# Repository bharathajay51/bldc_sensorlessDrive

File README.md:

# bldc_sensorlessDrive
Development of a 3-Phase Brushless Motor Driver.

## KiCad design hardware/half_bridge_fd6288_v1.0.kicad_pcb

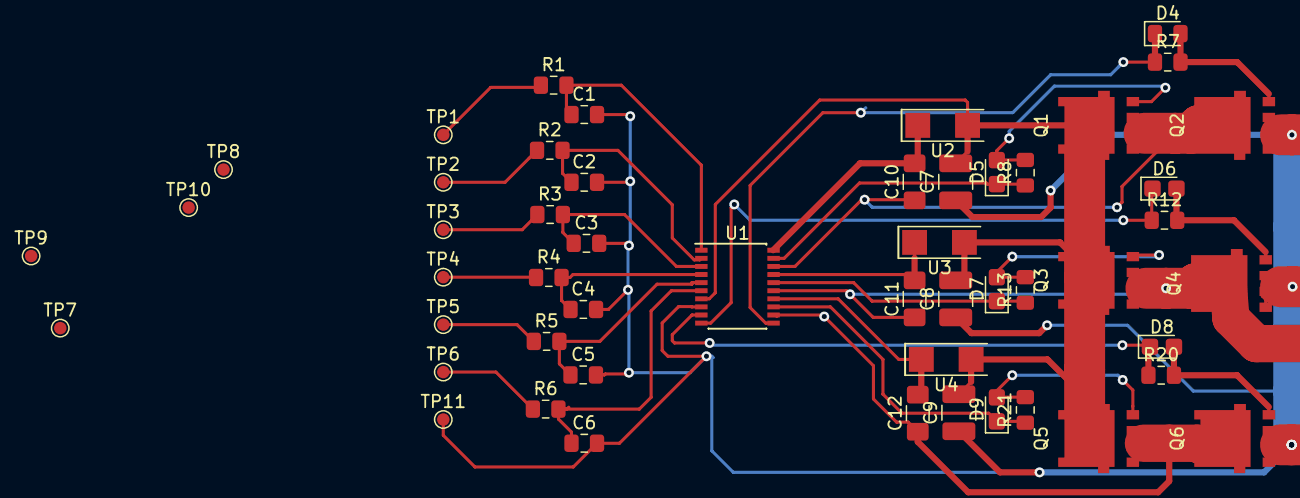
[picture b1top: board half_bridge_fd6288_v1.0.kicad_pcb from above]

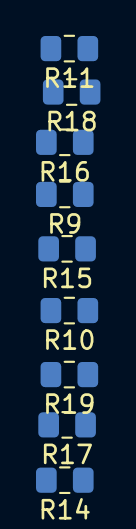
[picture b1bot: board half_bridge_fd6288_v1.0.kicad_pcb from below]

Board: 2 copper layers, 60 parts (9 on the bottom side), 36 nets.

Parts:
C1, C2, C3, C4, C5, C6: 33pF; C_0805_2012Metric_Pad1.15x1.40mm_HandSolder
C7, C8, C9: 1uF; C_1210_3225Metric_Pad1.42x2.65mm_HandSolder
C10, C11, C12: 100nF; C_1206_3216Metric_Pad1.42x1.75mm_HandSolder
D4: 1N4148; D_0805_2012Metric_Pad1.15x1.40mm_HandSolder
D5, D6, D7, D8, D9: 1N4148; D_0805_2012Metric_Castellated
Q1, Q2, Q3, Q4, Q5, Q6: Q_NMOS_DGS; NTMS5C430
R1, R2, R3, R4, R5, R6: 49.9; R_0805_2012Metric_Pad1.15x1.40mm_HandSolder
R7, R8, R12, R13, R20, R21: 3.3; R_0805_2012Metric_Pad1.15x1.40mm_HandSolder
R9, R14, R17: 33K; R_0805_2012Metric_Pad1.15x1.40mm_HandSolder
R10, R15, R18: 120K; R_0805_2012Metric_Pad1.15x1.40mm_HandSolder
R11, R16, R19: 3.3K; R_0805_2012Metric_Pad1.15x1.40mm_HandSolder
TP1: HIN_A; TestPoint_Pad_D1.0mm
TP2: HIN_B; TestPoint_Pad_D1.0mm
TP3: HIN_C; TestPoint_Pad_D1.0mm
TP4: LIN_A; TestPoint_Pad_D1.0mm
TP5: LIN_B; TestPoint_Pad_D1.0mm
TP6: LIN_C; TestPoint_Pad_D1.0mm
TP7: SENSE_A; TestPoint_Pad_D1.0mm
TP8: SENSE_B; TestPoint_Pad_D1.0mm
TP9, TP10: SENSE_C; TestPoint_Pad_D1.0mm
TP11: GND; TestPoint_Pad_D1.0mm
U1: FD6288; SSOP-20_4.4x6.5mm_P0.65mm
U2, U3, U4: MURA110T3

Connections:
GH_A: D5.1, R8.1, U1.19
GH_B: D7.1, R13.1, U1.16
GH_C: D9.1, R21.1, U1.13
GL_A: D4.1, R7.1, U1.11
GL_B: D6.1, R12.1, U1.10
GL_C: D8.1, R20.1, U1.9
GND: C1.2, C2.2, C3.2, C4.2, C5.2, C6.2, C7.1, C8.1, C9.1, Q2.3, Q4.3, Q6.3, R9.2, R14.2, R17.2, TP11.1, U1.8
HIN_A: R1.1, TP1.1
HIN_B: R2.1, TP2.1
HIN_C: R3.1, TP3.1
LIN_A: R4.1, TP4.1
LIN_B: R5.1, TP5.1
LIN_C: R6.1, TP6.1
unnamed: C1.1, R1.2, U1.1
unnamed: C2.1, R2.2, U1.2
unnamed: C3.1, R3.2, U1.3
unnamed: C4.1, R4.2, U1.4
unnamed: C5.1, R5.2, U1.5
unnamed: C6.1, R6.2, U1.6
unnamed: C10.2, U1.20, U2.1
unnamed: C11.2, U1.17, U3.1
unnamed: C12.2, U1.14, U4.1
unnamed: D4.2, Q2.2, R7.2
unnamed: D5.2, Q1.2, R8.2
unnamed: D6.2, Q4.2, R12.2
unnamed: D7.2, Q3.2, R13.2
unnamed: D8.2, Q6.2, R20.2
unnamed: D9.2, Q5.2, R21.2
PHASE_A: C10.1, Q1.3, Q2.1, R10.1, U1.18
PHASE_B: C11.1, Q3.3, Q4.1, R15.1, U1.15
PHASE_C: C12.1, Q5.3, Q6.1, R18.1, U1.12
SENSE_A: R9.1, R10.2, R11.2, TP7.1
SENSE_B: R14.1, R15.2, R16.2, TP8.1
SENSE_C: R17.1, R18.2, R19.2, TP9.1
SENSE_COM: R11.1, R16.1, R19.1, TP10.1
VCC: C7.2, C8.2, C9.2, Q1.1, Q3.1, Q5.1, U1.7, U2.2, U3.2, U4.2

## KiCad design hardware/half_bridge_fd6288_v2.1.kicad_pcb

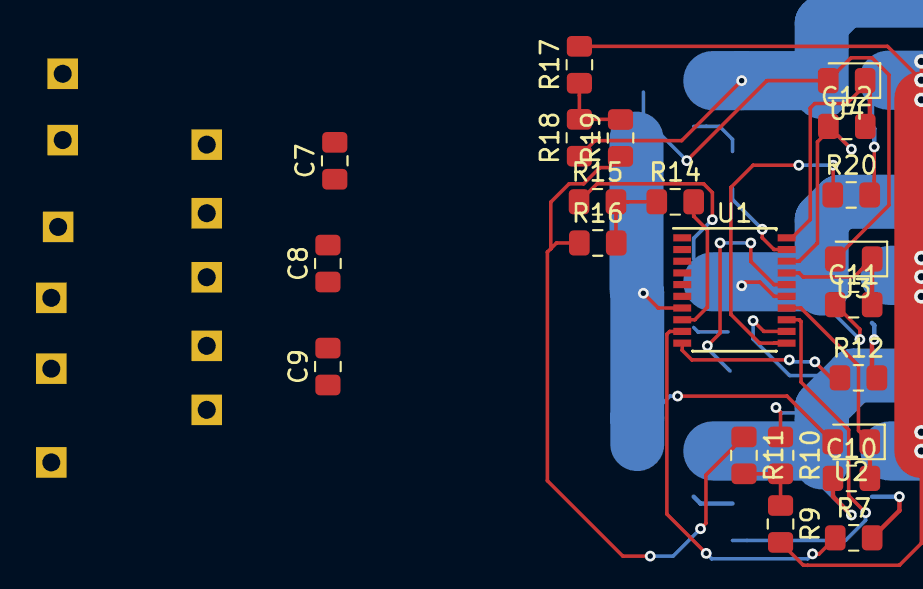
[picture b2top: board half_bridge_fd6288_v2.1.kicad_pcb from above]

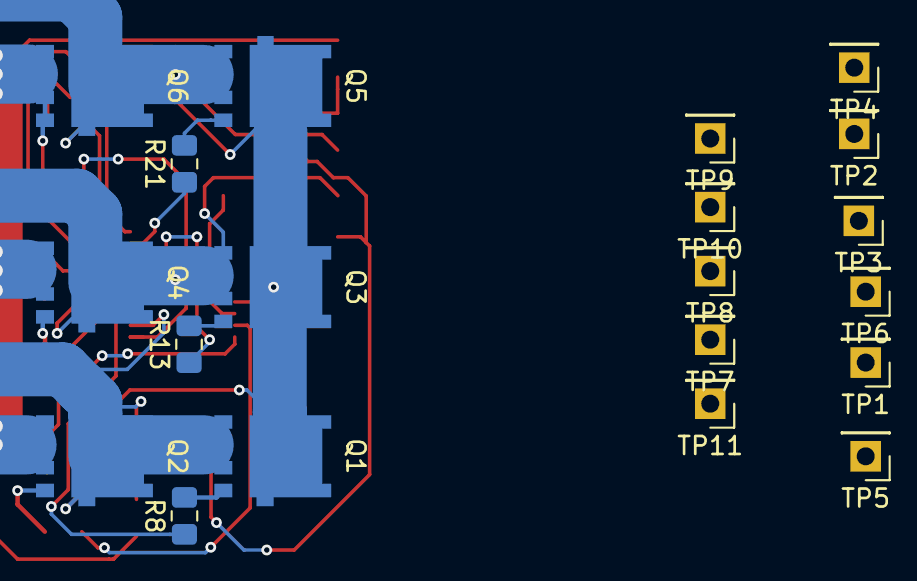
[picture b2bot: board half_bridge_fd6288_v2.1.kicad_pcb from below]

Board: 2 copper layers, 42 parts (20 on the bottom side), 29 nets.

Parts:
C7, C8, C9: 1uF; C_0805_2012Metric_Pad1.15x1.40mm_HandSolder
C10, C11, C12: 100nF; C_0805_2012Metric_Pad1.15x1.40mm_HandSolder
Q1, Q2, Q3, Q4, Q5, Q6: Q_NMOS_DGS; NTMS5C430
R7, R8, R12, R13, R20, R21: 3.3; R_0805_2012Metric_Pad1.15x1.40mm_HandSolder
R9, R14, R17: 33K; R_0805_2012Metric_Pad1.15x1.40mm_HandSolder
R10, R15, R18: 120K; R_0805_2012Metric_Pad1.15x1.40mm_HandSolder
R11, R16, R19: 3.3K; R_0805_2012Metric_Pad1.15x1.40mm_HandSolder
TP1: HIN_A; PinHeader_1x01_P2.54mm_Vertical
TP2: HIN_B; PinHeader_1x01_P2.54mm_Vertical
TP3: HIN_C; PinHeader_1x01_P2.54mm_Vertical
TP4: LIN_A; PinHeader_1x01_P2.54mm_Vertical
TP5: LIN_B; PinHeader_1x01_P2.54mm_Vertical
TP6: LIN_C; PinHeader_1x01_P2.54mm_Vertical
TP7: SENSE_A; PinHeader_1x01_P2.54mm_Vertical
TP8: SENSE_B; PinHeader_1x01_P2.54mm_Vertical
TP9, TP10: SENSE_C; PinHeader_1x01_P2.54mm_Vertical
TP11: GND; PinHeader_1x01_P2.54mm_Vertical
U1: FD6288; SSOP-20_4.4x6.5mm_P0.65mm
U2, U3, U4: MURA110T3; D_0805_2012Metric_Pad1.15x1.40mm_HandSolder

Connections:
GH_A: R8.1, U1.13
GH_B: R13.1, U1.16
GH_C: R21.1, U1.19
GL_A: R7.1, U1.9
GL_B: R12.1, U1.10
GL_C: R20.1, U1.11
GND: C7.1, C8.1, C9.1, Q2.3, Q4.3, Q6.3, R9.2, R14.2, R17.2, TP11.1, U1.8
HIN_A: TP1.1, U1.3
HIN_B: TP2.1, U1.2
HIN_C: TP3.1, U1.1
LIN_B: TP5.1, U1.5
LIN_C: TP6.1, U1.4
unnamed: C10.2, U1.14, U2.1
unnamed: C11.2, U1.17, U3.1
unnamed: C12.2, U1.20, U4.1
unnamed: Q1.2, R8.2
unnamed: Q2.2, R7.2
unnamed: Q3.2, R13.2
unnamed: Q4.2, R12.2
unnamed: Q5.2, R21.2
unnamed: Q6.2, R20.2
PHASE_A: C10.1, Q1.3, Q2.1, R10.1, U1.12
PHASE_B: C11.1, Q3.3, Q4.1, R15.1, U1.15
PHASE_C: C12.1, Q5.3, Q6.1, R18.1, U1.18
SENSE_A: R9.1, R10.2, R11.2, TP7.1
SENSE_B: R14.1, R15.2, R16.2, TP8.1
SENSE_C: R17.1, R18.2, R19.2, TP9.1
SENSE_COM: R11.1, R16.1, R19.1, TP10.1
VCC: C7.2, C8.2, C9.2, Q1.1, Q3.1, Q5.1, U1.7, U2.2, U3.2, U4.2

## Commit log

2020-08-18 Initial Commits
